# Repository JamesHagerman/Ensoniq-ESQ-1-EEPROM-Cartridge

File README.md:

# Ensoniq ESQ-1 EEPROM Cartridge

This repo contains an open source hardware design for a EEPROM-based patch storage cartridge for the Ensoniq ESQ-1 and SQ-80 hybrid synthesizers..

## Assembly Details

*Note: Do not populate C1! Field testing has shown that it decreases stability of the cartridge.*

Latest assembly instructions and errata can be found in the PDF at the root of this repo.

The PCB is designed to support AT28C64 and AT28C256 (or similar) EEPROM's. The larger EEPROM option can be controlled using 2 switches (purple wires in the photo below).

The cartridge can also be configured as a "read-only" cartridge with some reducion in parts count.

The current 3D printed enclosure design is provided as a Fusion 360 file. The two halves of the case are inteded to be held together either using a press fit or with clear packing tape. Not elegant, but it works.

## Where can I purchase one?

*Note: PCBs are currently out of stock at the ZenSynth Tindie store and Reverb pending an updated design and PCB run. Existing PCBs can be purchased from Mono Tanz here: https://monotanz.de/product/diy-ensoniq-esq-1-sq-80-eeprom-cartridge/*

Unpopulated PCB's can be ordered from the ZenSynth store on Tindie: 

https://www.tindie.com/products/zensynth/oshdiy-ensoniq-esq-1sq-80-eeprom-cartridge/

Or on Reverb:

https://reverb.com/item/62807297-ensoniq-esq-1-sq-80-eeprom-cartridge-pcb-direct-from-pcb-designer

Enclosures can be 3D printed using the STL files provided in this repo. I had good luck printing the cartriges in PETG on a Prusa i3 mk3.

## BOM?

I don't follow an exact Bill of Materials, but I exported this from my Mouser project.

*Note: Please make sure you check which EEPROM you're ordering! You only need one but two are listed below!*

```
ENSONIQ ESQ-1/SQ-80 EEPROM CARTRIDGE									
Mouser #	Mfr. #	Manufacturer	Customer #	Description	RoHS	Lifecycle	Order Qty.	Price (USD)	Ext.: (USD)
556-AT28C64B15PU	AT28C64B-15PU	Microchip		EEPROM 64K 8K x 8 150 ns 4.5V-5.5V	RoHS Compliant		1	$5.84	$5.84
556-AT28C25615PU	AT28C256-15PU	Microchip		EEPROM 256K 32K x 8 150 ns 4.5V-5.5V	RoHS Compliant		1	$12.33	$12.33
652-4607X-1LF-4.7K	4607X-101-472LF	Bourns		Resistor Networks & Arrays 7pins 4.7Kohms Bussed	RoHS Compliant By Exemption		2	$0.47	$0.94
594-K103J20C0GH53H5G	K103J20C0GH53H5G	Vishay		Multilayer Ceramic Capacitors MLCC - Leaded 100V 10nF 5% C0G e3 Auto	RoHS Compliant		1	$0.75	$0.75
279-LR1F3K3	LR1F3K3	TE Connectivity		Metal Film Resistors - Through Hole 3.3KOhm 3/5W 50PPM	RoHS Compliant		2	$0.16	$0.32
571-1-2199299-2	1-2199299-2	TE Connectivity		IC & Component Sockets 28P DIP SKT 600 CL LADDER	RoHS Compliant		1	$0.67	$0.67
```

*Additional Note: These EEPROM's have been hit by the component shortage. Microchip/Atmel EEPROM chips would be ideal, but the part only really need to be pin compatible 28c64/28c256 EEPROM's. Check Jameco's stock if you can't find any from your normal supplier! They have a good history of keeping 'em on the shelves. (i.e. https://www.jameco.com/z/28C256-25-Major-Brands-IC-28C256-25IC-EEPROM-256K-Bit-CMOS-Parallel_74878.html)*

## Assembly Instructions?

Instructions to assembly the board can be found in the `assembly-notes-and-schematic-vX.X.X.pdf` file in the root directory of this repo.

## Initialization Steps

After assembly, you have to "initialize" the cartridge before using it. You can do this by saving the synths internal patches to EEPROM. Here are some steps:

```
    Power up the synth
    Plug in the cartridge
    Press “STORAGE”
    Press the button under “CARTRIDGE”
    Press the button for “INT TO CART A” or “INT TO CART B”
    Press the button for “YES”
```
## Errata

### Writes are unstable

If you are having issues initializing the cartridge or writing patches to the cartridge, *please consider removing `C1` from the board and try the initialization process again.*

Other builders ran into stability issues and helped greatly in identifying potential fixes (Thanks Ivan!). This was somewhat difficult to track down due to the age and various condition of people's Ensoniq synths.

### Cartridge detect circuitry is incorrect

As noted in the errata section of the schematic PDF, please (i.e. do not populate) R2, do not cut JP1, and do not short Pin 2 of J1 to Vcc at any time.

There are no good examples of the associated `CPRES` line being used effectively on other cartridges and I didn't do enough testing before getting boards assembled. I'll remove these components if another run of boards ends up happening.

## I'm stuck. How do I get help?

If you purchased the board from me, you should have my contact information. Otherwise, please consider opening a new [GitHub issue](https://github.com/JamesHagerman/Ensoniq-ESQ-1-EEPROM-Cartridge/issues) including additional context about where you're stuck. I'll do my best to help! 

## Additional Resources

A very special thanks to Rainer Buchty for his help bringing this project to life! Thank you for the chats and resources!

If you haven't already found his wonderfully detailed site dedicated to Ensoniq synthesizers, you're missing out: http://www.buchty.net/ensoniq/

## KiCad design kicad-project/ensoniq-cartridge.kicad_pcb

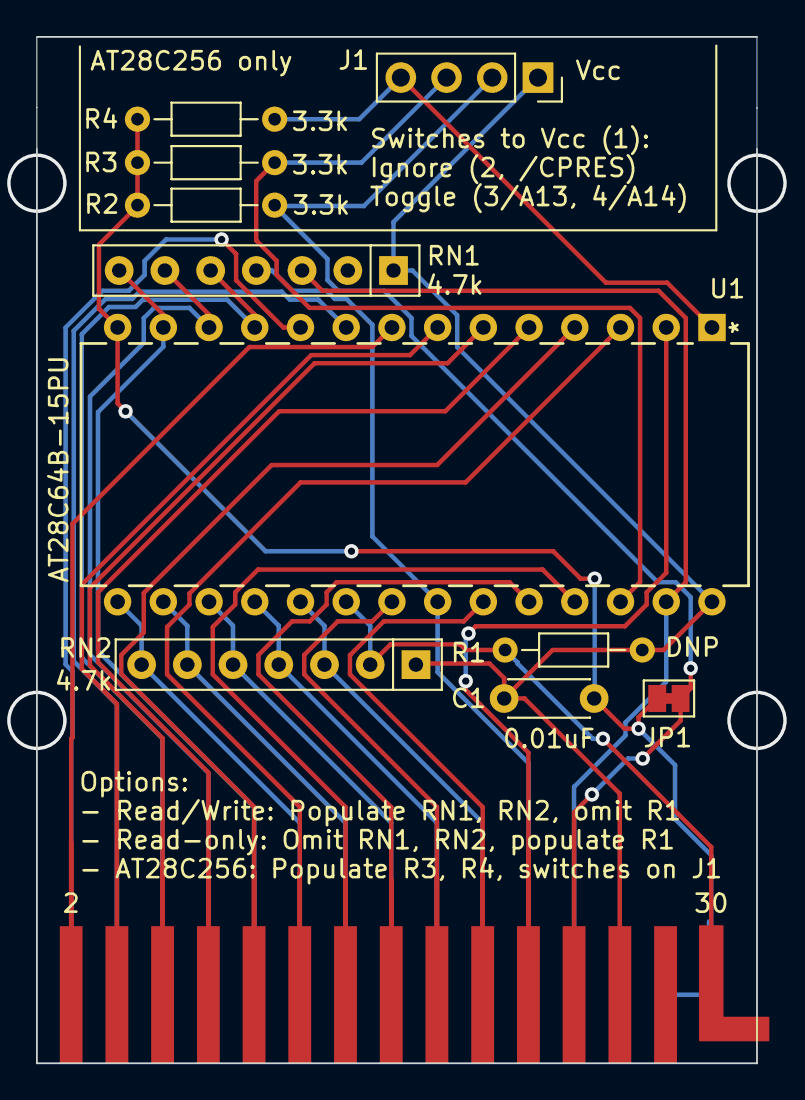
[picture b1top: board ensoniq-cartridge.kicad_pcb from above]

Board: 2 copper layers, 40.0 x 57.0 mm, 11 parts (0 on the bottom side), 29 nets.

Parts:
C1: 0.01uF; C_Disc_D4.3mm_W1.9mm_P5.00mm
J1: Conn_01x04_Male; PinSocket_1x04_P2.54mm_Vertical
JP1: SolderJumper_2_Bridged; SolderJumper-2_P1.3mm_Bridged_Pad1.0x1.5mm
R1: DNP; R_Axial_DIN0204_L3.6mm_D1.6mm_P7.62mm_Horizontal
R2, R3, R4: 3.3k; R_Axial_DIN0204_L3.6mm_D1.6mm_P7.62mm_Horizontal
RN1, RN2: 4.7k; R_Array_SIP7
U1: AT28C64B-15PU
U2: ensoniq-cartridge-edge-connector

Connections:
A0-c1: U1.10, U2.1
A1-c3: U1.9, U2.3
A2-c2: U1.8, U2.2
A3-c4: U1.7, U2.4
A4-c6: U1.6, U2.6
A5-c8: U1.5, U2.8
A6-c10: U1.4, U2.10
A7-c12: U1.3, U2.12
A8-c14: U1.25, U2.14
A9-c16: U1.24, U2.16
A10-c18: U1.21, U2.18
A11-c20: U1.23, U2.20
A12-c22: U1.2, U2.22
A13-optional: J1.3, R3.2, U1.26
A14-optional: J1.4, R4.2, U1.1
CE-c30: R1.1, RN2.2, U1.20, U2.30
CPRES-c24: J1.2, JP1.1, R2.2, U2.24
D0-c5: RN1.5, U1.11, U2.5
D1-c7: RN1.6, U1.12, U2.7
D2-c9: RN1.7, U1.13, U2.9
D3-c11: RN2.7, U1.15, U2.11
D4-c13: RN2.6, U1.16, U2.13
D5-c15: RN2.5, U1.17, U2.15
D6-c17: RN2.4, U1.18, U2.17
D7-c18: RN2.3, U1.19, U2.19
GND: C1.2, JP1.2, R2.1, R3.1, R4.1, U1.14, U2.27, U2.29
OE-c21: RN1.4, U1.22, U2.21
VCC: C1.1, J1.1, R1.2, RN1.1, RN2.1, U1.28, U2.26
WE-c23: RN1.3, U1.27, U2.23

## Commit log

2022-06-01 Adding KiCad PCB files. Adding Gerber files. Adding Enclosure Fusion 360 file and STL files. Adding BoM. Adding PDF documenting latest assembly instructions and errata.
2022-06-01 Adding Readme and reference photos of the completed board and enclosure.
2022-10-12 Adding component details to the README
2022-11-02 Update README.md
    Adding Reverb store link. Adding initialization steps.
2022-11-02 Update README.md
    Adding notes about sourcing an enclosure
2022-11-02 Update README.md
    Adding note about rogue seller on Reverb
2022-11-02 Update README.md
    Adding notes about the EEPROM's on the BoM and adding suggestion of using Jameco to source hard-to-find parts
2022-11-02 Update README.md
    Oops. Microchip and Atmel are kinda a thing now, right?
2022-12-05 Updating schematic with initialization steps and adding schematic image to repo.
2023-01-09 Updating schamtic and PDF build instructions to be more human readable.
2023-01-16 Updating README.me and assembly notes and schematic PDF to include stability suggestions relating to C1.
2024-09-03 Update README.md to trigger pages build
2025-05-29 Update README.md with note about C1 instability and updated source for PCBs
